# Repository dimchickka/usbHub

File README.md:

# USB PD Charger — 20 портов

Проект KiCad 9.0.6: GD32F470, SDRAM, дисплей 480×272, 20 зарядных USB-C портов.

Открывать **USB_PD_Charger_hw/USB_PD_Charger.kicad_pro**.
Единственная рабочая плата — **USB_PD_Charger_hw/USB_PD_Charger.kicad_pcb**.
Три файла схемы, fp-lib-table, sym-lib-table и каталоги libs входят в проект и нужны для его редактирования. libs/Symbols/ProjectCache содержит рабочие проектные библиотеки, это не временный кеш.

- `USB_PD_Charger_hw/release/FINAL_REVIEW.md` — итоговая проверка и открытые параметры заказа.
- `USB_PD_Charger_hw/release/USB_PD_Charger_fabrication.zip` — Gerber и сверление для изготовления платы.
- `USB_PD_Charger_hw/release/assembly` — справочная BOM и координаты монтажа.
- `USB_PD_Charger_fw` — исходники прошивки.
- `documents` — даташиты.

Финальные DRC, ERC и сверка схемы с платой: 0 ошибок и 0 предупреждений; неподключений 0. Разброс 38 линий SDRAM — 0,727 мм.

Перед заказом выбрать финишное покрытие и согласовать стек 4 слоя / 1,5 мм. F1–F5: выбран Bel 0680H9150-05, 15 А / 125 В DC. Обязательные требования к пяти вводам, БП и испытаниям — в USB_PD_Charger_hw/release/FUSE_SELECTION.md. Нагрузочные испытания устройства на 1 кВт не проводились; геометрическая проверка их не заменяет.

При изменении платы повторить проверки и обновить release. Промежуточные платы, логи трассировки и старые резервные копии вынесены из рабочей директории.

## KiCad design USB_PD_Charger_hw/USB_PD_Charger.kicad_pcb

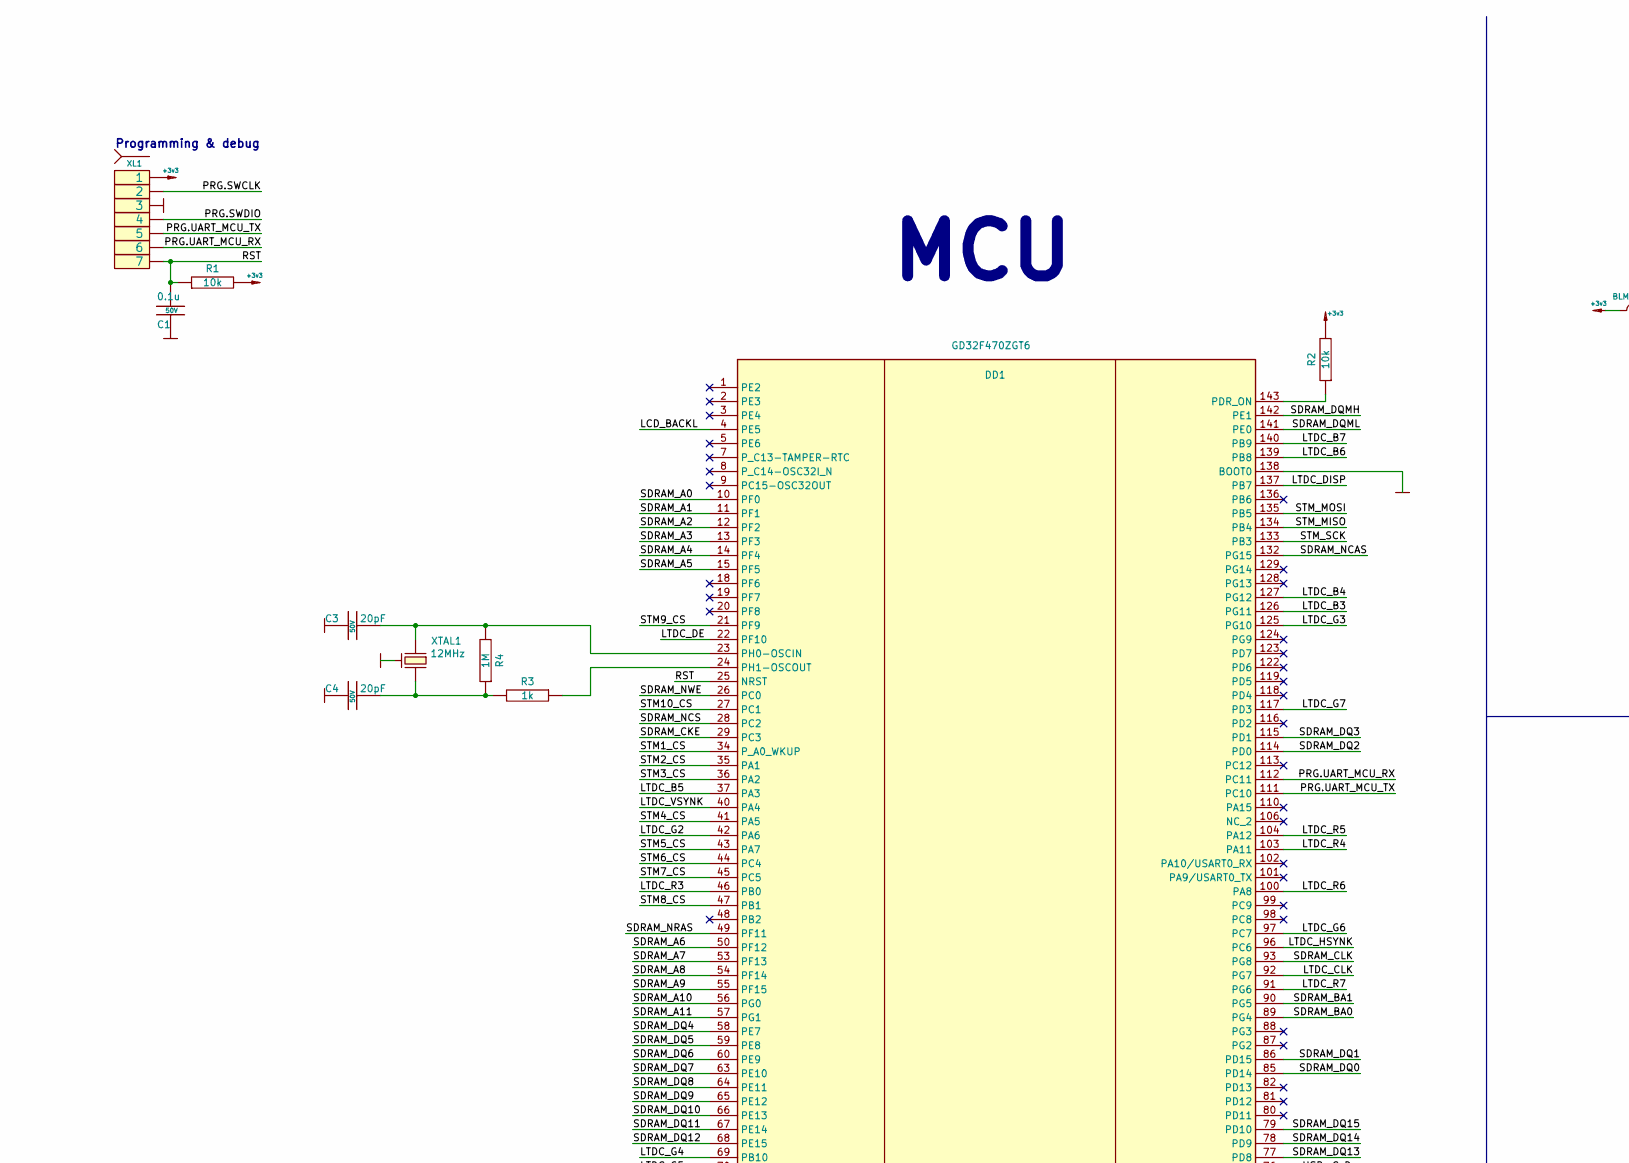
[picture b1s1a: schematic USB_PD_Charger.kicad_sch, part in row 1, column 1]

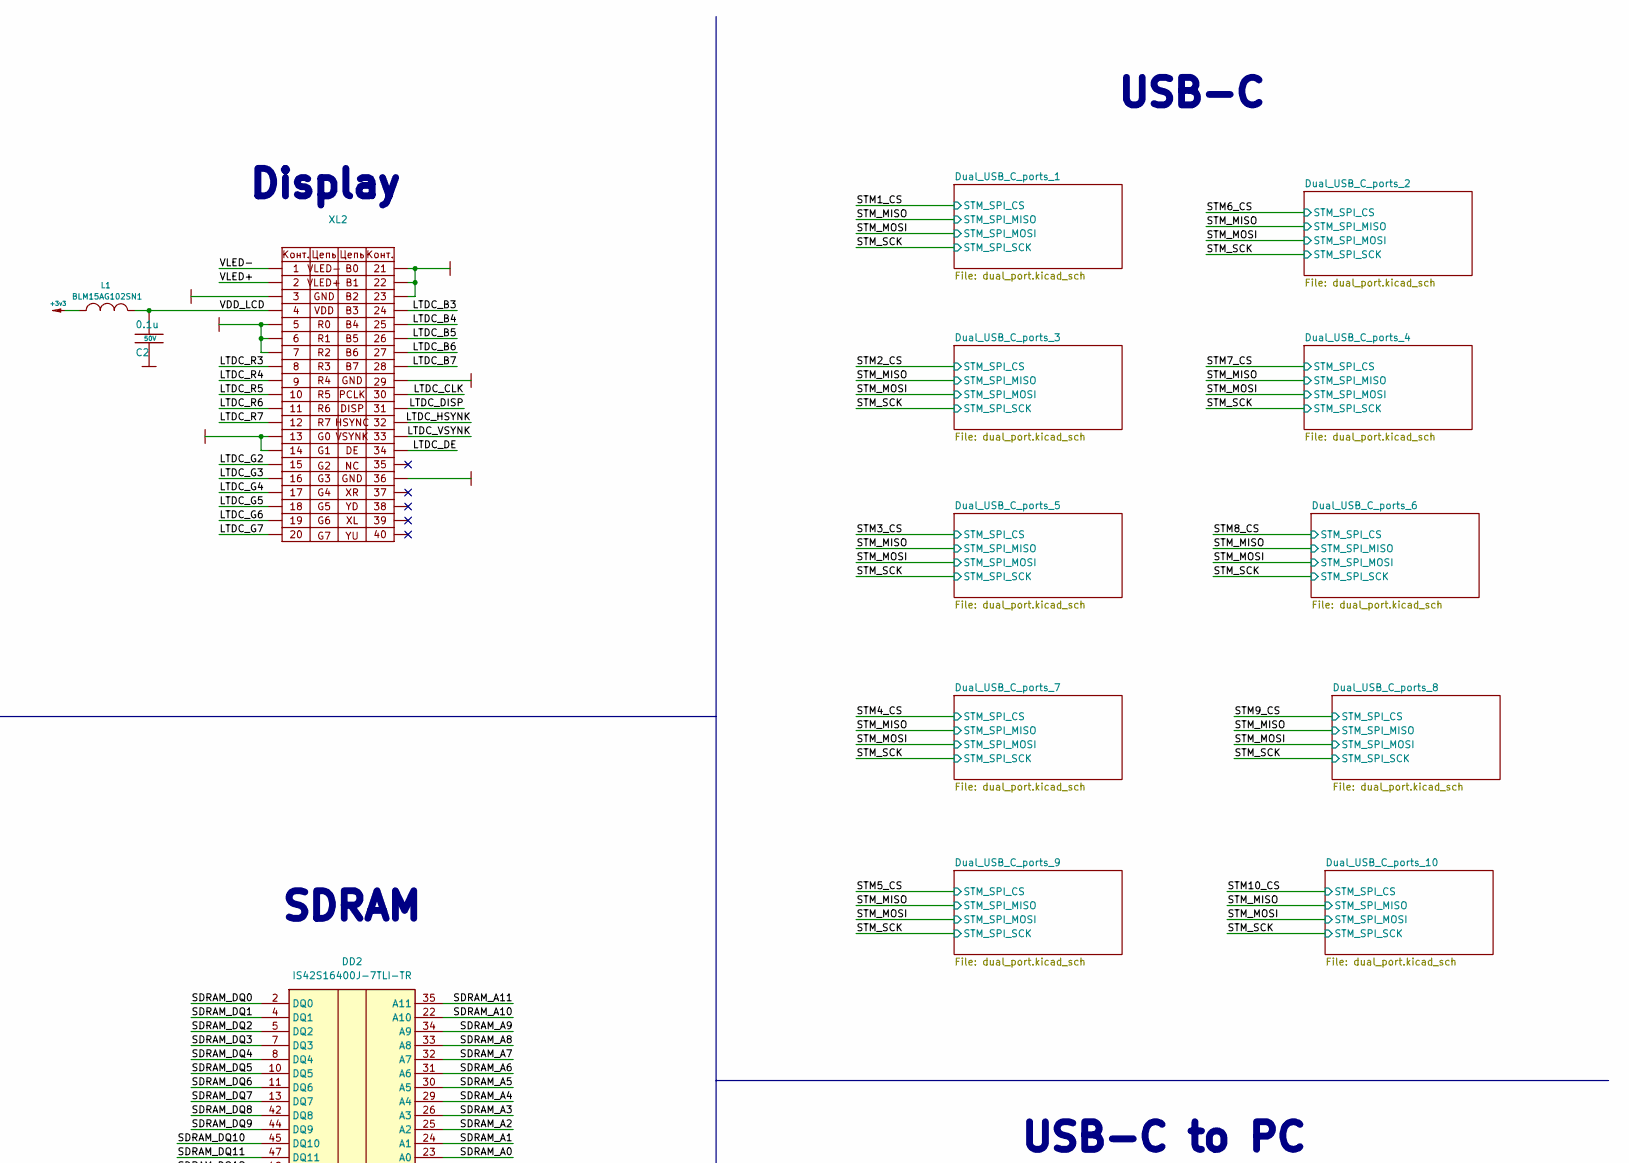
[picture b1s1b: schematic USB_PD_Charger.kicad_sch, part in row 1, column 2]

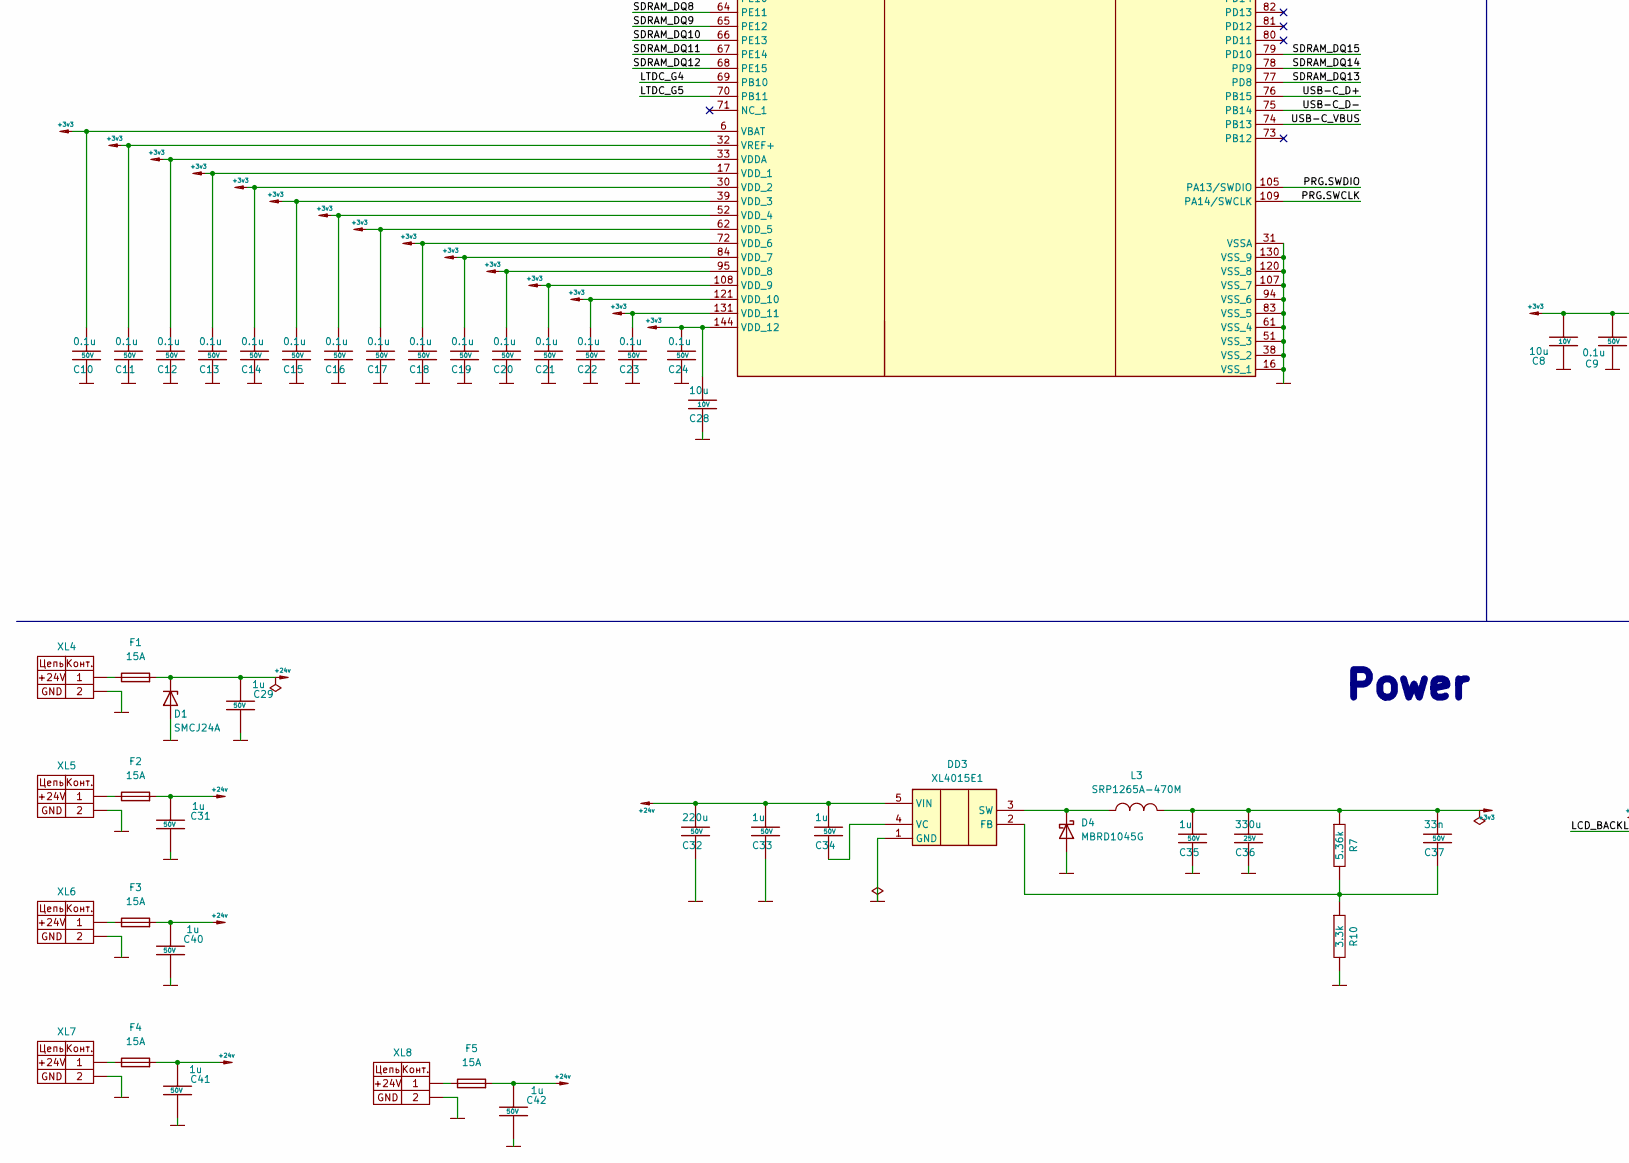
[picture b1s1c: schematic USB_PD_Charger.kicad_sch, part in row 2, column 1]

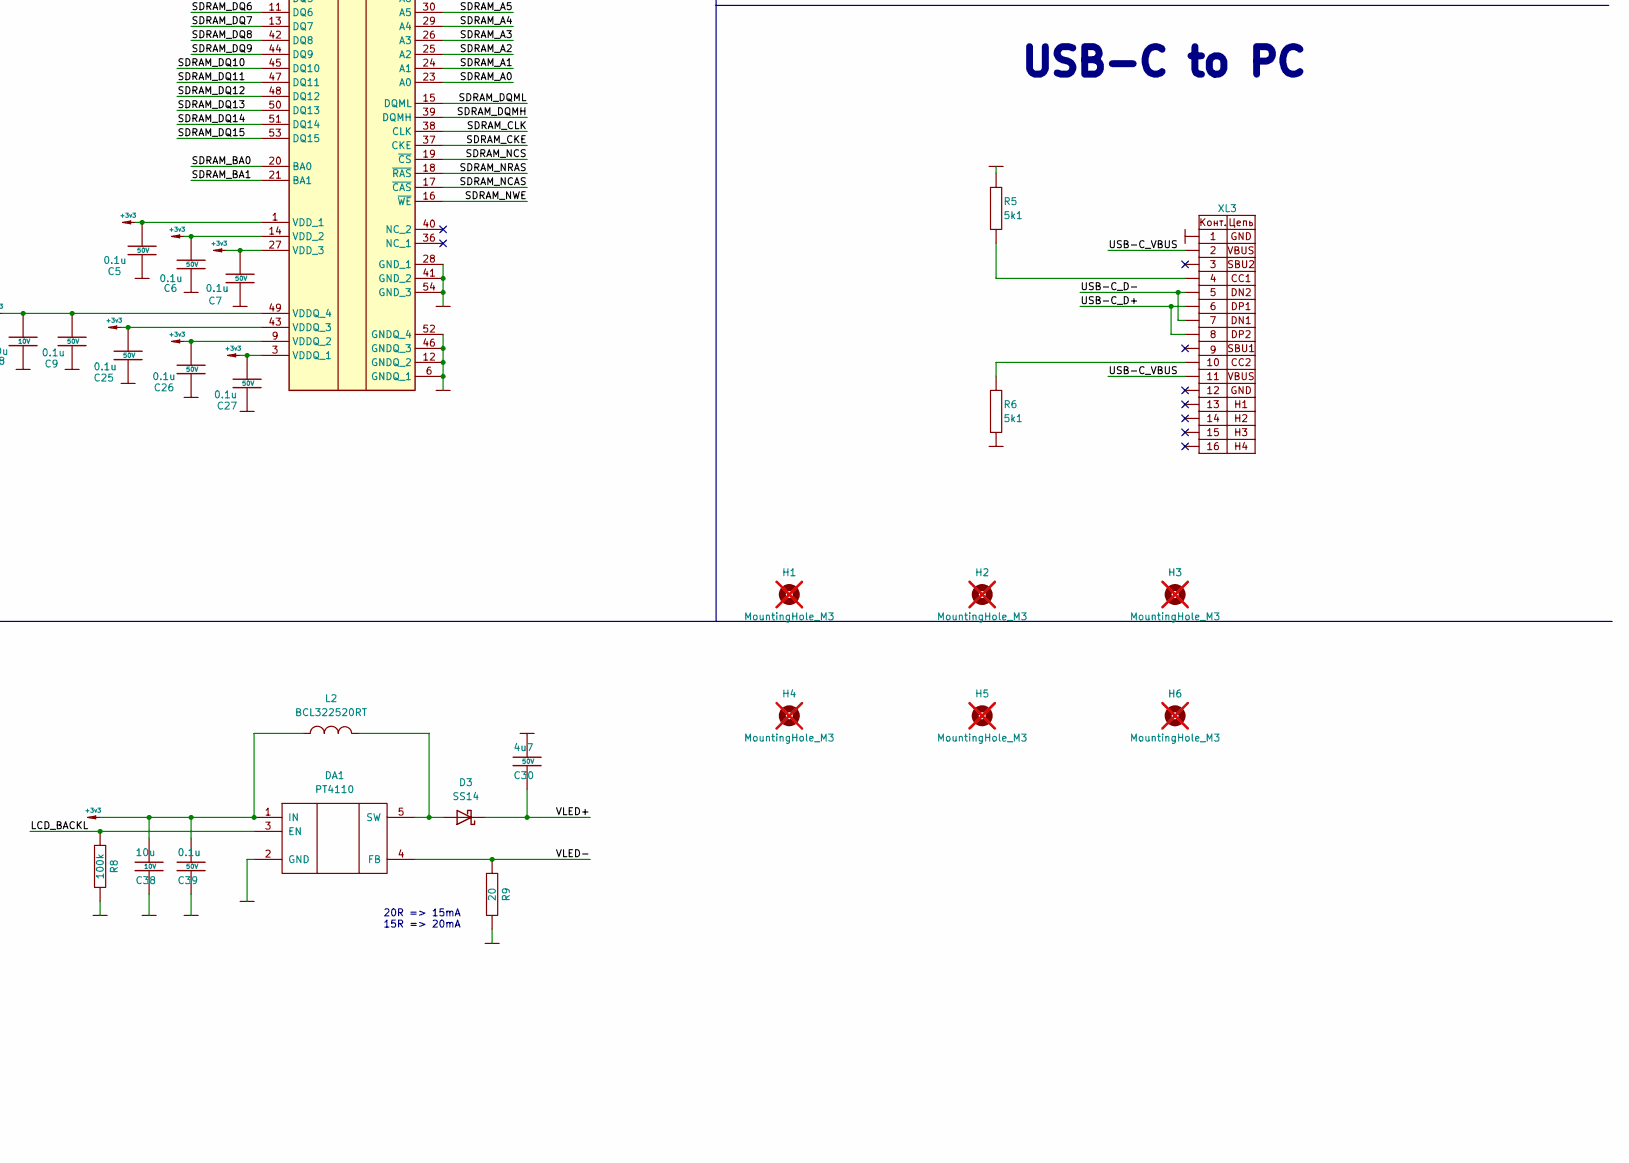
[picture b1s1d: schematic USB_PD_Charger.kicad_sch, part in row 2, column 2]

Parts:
C1: 0.1u; CAP_0603_Silks_Board; Tolerance 10%; Voltage 50V
C2, C5, C6, C7, C9, C10, C11, C12, C13, C14, C15, C16, C17, C18, C19, C20, C21, C22, C23, C24, C25, C26, C27, C39: 0.1u; CAP_0603_Silks; Tolerance 10%; Voltage 50V
C3, C4: 20pF; CAP_0603_Silks; Tolerance 20%; Voltage 50V
C8, C28: 10u; CAP_0603_Silks; Tolerance 20%; Voltage 10V
C29, C31, C33, C34, C35, C40, C41, C42: 1u; CAP_0603_Silks; Tolerance 10%; Voltage 50V
C30: 4u7; C_1206_3216Metric; Tolerance 10%; Voltage 50V
C32: 220u; CP_Elec_10x10.5; Tolerance 10%; Voltage 50V
C36: 330u; CP_Elec_10x10.5; Tolerance 20%; Voltage 25V
C37: 33n; CAP_0603_Silks; Tolerance 10%; Voltage 50V
C38: 10u; CP_EIA-3216-18_Kemet-A; Tolerance 10%; Voltage 10V
D1: SMCJ24A; D_SMB-SMC_Universal_Handsoldering
D3: SS14; D_SMA
D4: MBRD1045G; MBRD1045G_DPAK
DA1: PT4110; SOT89_5_Board
DD1: GD32F470ZGT6; QFP50P2200X2200X160-144N; Manufacturer_Part_Number GD32F470ZGT6
DD2: IS42S16400J-7TLI-TR; SOP80P1176X120-54N; Manufacturer_Part_Number IS42S16400J-7TLI-TR; Mouser Part Number 870-42S16400J7TLITR
DD3: XL4015E1; TO-263-5_TabPin3
F1, F2, F3, F4, F5: 15A; FUSC6125X279N; VoltageRating 125VDC; MPN 0680H9150-05
H1, H2, H3, H4, H5, H6: MountingHole_M3; MountingHole_3.2mm_M3_Clearance7.4; not fitted
L1: BLM15AG102SN1; IND_0402; Tolerance 20%
L2: BCL322520RT; L_1210_3225Metric; Tolerance 20%
L3: SRP1265A-470M; L_TaiTech_TMPC1265_13.5x12.5mm; Tolerance 20%
R1: 10k; RES_0603_Silks_Board; Tolerance 1%
R2: 10k; RES_0603_Silks; Tolerance 1%
R3: 1k; RES_0603_Silks; Tolerance 0.1%
R4: 1M; RES_0603_Silks; Tolerance 1%
R5, R6: 5k1; RES_0603_Silks; Tolerance 1%
R7: 5.36k; RES_0603_Silks; Tolerance 1%
R8: 100k; RES_0603_Silks; Tolerance 1%
R9: 20; RES_0603_Silks; Tolerance 1%
R10: 3.3k; RES_0603_Silks; Tolerance 1%
XL1: SOCKET_7; PLS-7_LOCK
XL2: Omron_XF2M-4015-1A_1x40-1MP_P0.5mm_Horizontal
XL3: USBC_DS1144-18
XL4, XL5, XL6, XL7, XL8: Screw_Terminal; Screw_Terminal_footprint; Manufacturer_Part_Number 1933613; Mouser Part Number 651-1933613
XTAL1: 12MHz; 03225C4

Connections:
+3v3: C5.1, C6.1, C7.1, C8.1, C9.1, C10.1, C11.1, C12.1, C13.1, C14.1, C15.1, C16.1, C17.1, C18.1, C19.1, C20.1, C21.1, C22.1, C23.1, C24.1, C25.1, C26.1, C27.1, C28.1, C35.1, C36.1, C37.1, C38.1, C39.1, DA1.1 (IN), DD1.6 (VBAT), DD1.17 (VDD_1), DD1.30 (VDD_2), DD1.32 (VREF+), DD1.33 (VDDA), DD1.39 (VDD_3), DD1.52 (VDD_4), DD1.62 (VDD_5), DD1.72 (VDD_6), DD1.84 (VDD_7), DD1.95 (VDD_8), DD1.108 (VDD_9), DD1.121 (VDD_10), DD1.131 (VDD_11), DD1.144 (VDD_12), DD2.1 (VDD_1), DD2.3 (VDDQ_1), DD2.9 (VDDQ_2), DD2.14 (VDD_2), DD2.27 (VDD_3), DD2.43 (VDDQ_3), DD2.49 (VDDQ_4), L1.2, L2.2, L3.1, R1.2, R2.2, R7.1, XL1.1; also elsewhere on the board
+24v: C29.2, C31.2, C32.1, C33.1, C34.1, C40.2, C41.2, C42.2, D1.1 (K), DD3.5 (VIN), F1.2, F2.2, F3.2, F4.2, F5.2; also elsewhere on the board
/LCD_BACKL: DA1.3 (EN), DD1.4 (PE5), R8.1
/LTDC_B3: DD1.126 (PG11), XL2.24 (+3.3V)
/LTDC_B4: DD1.127 (PG12), XL2.25 (r8t0)
/LTDC_B5: DD1.37 (PA3), XL2.26 (r8p1)
/LTDC_B6: DD1.139 (PB8), XL2.27 (+3.3V)
/LTDC_B7: DD1.140 (PB9), XL2.28 (r9t0)
/LTDC_CLK: DD1.92 (PG7), XL2.30 (+3.3V)
/LTDC_DE: DD1.22 (PF10), XL2.34 (+3.3V)
/LTDC_DISP: DD1.137 (PB7), XL2.31 (+3.3V)
/LTDC_G2: DD1.42 (PA6), XL2.15 (+3.3V)
/LTDC_G3: DD1.125 (PG10), XL2.20 (r6t1)
/LTDC_G4: DD1.69 (PB10), XL2.19 (r6t0)
/LTDC_G5: DD1.70 (PB11), XL2.18 (+3.3V)
/LTDC_G6: DD1.97 (PC7), XL2.17 (r5t1)
/LTDC_G7: DD1.117 (PD3), XL2.16 (r5t0)
/LTDC_HSYNK: DD1.96 (PC6), XL2.32 (r7t0)
/LTDC_R3: DD1.46 (PB0), XL2.8 (r2t1)
/LTDC_R4: DD1.103 (PA11), XL2.9 (+3.3V)
/LTDC_R5: DD1.104 (PA12), XL2.10 (r3t0)
/LTDC_R6: DD1.100 (PA8), XL2.11 (r3t1)
/LTDC_R7: DD1.91 (PG6), XL2.12 (+3.3V)
/LTDC_VSYNK: DD1.40 (PA4), XL2.33 (r7t1)
/PRG.SWCLK: DD1.109 (PA14/SWCLK), XL1.2
/PRG.SWDIO: DD1.105 (PA13/SWDIO), XL1.4
/PRG.UART_MCU_RX: DD1.112 (PC11), XL1.6
/PRG.UART_MCU_TX: DD1.111 (PC10), XL1.5
/RST: C1.1, DD1.25 (NRST), R1.1, XL1.7
/SDRAM_A0: DD1.10 (PF0), DD2.23 (A0)
/SDRAM_A1: DD1.11 (PF1), DD2.24 (A1)
/SDRAM_A2: DD1.12 (PF2), DD2.25 (A2)
/SDRAM_A3: DD1.13 (PF3), DD2.26 (A3)
/SDRAM_A4: DD1.14 (PF4), DD2.29 (A4)
/SDRAM_A5: DD1.15 (PF5), DD2.30 (A5)
/SDRAM_A6: DD1.50 (PF12), DD2.31 (A6)
/SDRAM_A7: DD1.53 (PF13), DD2.32 (A7)
/SDRAM_A8: DD1.54 (PF14), DD2.33 (A8)
/SDRAM_A9: DD1.55 (PF15), DD2.34 (A9)
/SDRAM_A10: DD1.56 (PG0), DD2.22 (A10)
/SDRAM_A11: DD1.57 (PG1), DD2.35 (A11)
/SDRAM_BA0: DD1.89 (PG4), DD2.20 (BA0)
/SDRAM_BA1: DD1.90 (PG5), DD2.21 (BA1)
/SDRAM_CKE: DD1.29 (PC3), DD2.37 (CKE)
/SDRAM_CLK: DD1.93 (PG8), DD2.38 (CLK)
/SDRAM_DQ0: DD1.85 (PD14), DD2.2 (DQ0)
/SDRAM_DQ1: DD1.86 (PD15), DD2.4 (DQ1)
/SDRAM_DQ2: DD1.114 (PD0), DD2.5 (DQ2)
/SDRAM_DQ3: DD1.115 (PD1), DD2.7 (DQ3)
/SDRAM_DQ4: DD1.58 (PE7), DD2.8 (DQ4)
/SDRAM_DQ5: DD1.59 (PE8), DD2.10 (DQ5)
/SDRAM_DQ6: DD1.60 (PE9), DD2.11 (DQ6)
/SDRAM_DQ7: DD1.63 (PE10), DD2.13 (DQ7)
/SDRAM_DQ8: DD1.64 (PE11), DD2.42 (DQ8)
/SDRAM_DQ9: DD1.65 (PE12), DD2.44 (DQ9)
/SDRAM_DQ10: DD1.66 (PE13), DD2.45 (DQ10)
/SDRAM_DQ11: DD1.67 (PE14), DD2.47 (DQ11)
/SDRAM_DQ12: DD1.68 (PE15), DD2.48 (DQ12)
/SDRAM_DQ13: DD1.77 (PD8), DD2.50 (DQ13)
/SDRAM_DQ14: DD1.78 (PD9), DD2.51 (DQ14)
/SDRAM_DQ15: DD1.79 (PD10), DD2.53 (DQ15)
/SDRAM_DQMH: DD1.142 (PE1), DD2.39 (DQMH)
/SDRAM_DQML: DD1.141 (PE0), DD2.15 (DQML)
/SDRAM_NCAS: DD1.132 (PG15), DD2.17 (~CAS)
/SDRAM_NCS: DD1.28 (PC2), DD2.19 (~CS)
/SDRAM_NRAS: DD1.49 (PF11), DD2.18 (~RAS)
/SDRAM_NWE: DD1.26 (PC0), DD2.16 (~WE)
/STM1_CS: DD1.34 (P_A0_WKUP); also elsewhere on the board
/STM2_CS: DD1.35 (PA1); also elsewhere on the board
/STM3_CS: DD1.36 (PA2); also elsewhere on the board
/STM4_CS: DD1.41 (PA5); also elsewhere on the board
/STM5_CS: DD1.43 (PA7); also elsewhere on the board
/STM6_CS: DD1.44 (PC4); also elsewhere on the board
/STM7_CS: DD1.45 (PC5); also elsewhere on the board
/STM8_CS: DD1.47 (PB1); also elsewhere on the board
/STM9_CS: DD1.21 (PF9); also elsewhere on the board
/STM10_CS: DD1.27 (PC1); also elsewhere on the board
/STM_MISO: DD1.134 (PB4); also elsewhere on the board
/STM_MOSI: DD1.135 (PB5); also elsewhere on the board
/STM_SCK: DD1.133 (PB3); also elsewhere on the board
/USB-C_D+: DD1.76 (PB15), XL3.A6 (+3.3V), XL3.B6 (r2t1)
/USB-C_D-: DD1.75 (PB14), XL3.A7 (r2t0), XL3.B7 (r1t1)
/USB-C_VBUS: DD1.74 (PB13), XL3.A4B9 (rot1), XL3.B4A9 (r3t1)
/VDD_LCD: C2.1, L1.1, XL2.4 (r1t0)
/VLED+: C30.2, D3.1 (K), XL2.2 (rot1)
/VLED-: DA1.4 (FB), R9.1, XL2.1 (rot0)
GND: C1.2, C2.2, C3.2, C4.2, C5.2, C6.2, C7.2, C8.2, C9.2, C10.2, C11.2, C12.2, C13.2, C14.2, C15.2, C16.2, C17.2, C18.2, C19.2, C20.2, C21.2, C22.2, C23.2, C24.2, C25.2, C26.2, C27.2, C28.2, C29.1, C30.1, C31.1, C32.2, C33.2, C35.2, C36.2, C38.2, C39.2, C40.1, C41.1, C42.1, D1.2 (A), D4.2 (A), DA1.2 (GND), DD1.16 (VSS_1), DD1.31 (VSSA), DD1.38 (VSS_2), DD1.51 (VSS_3), DD1.61 (VSS_4), DD1.83 (VSS_5), DD1.94 (VSS_6), DD1.107 (VSS_7), DD1.120 (VSS_8), DD1.130 (VSS_9), DD1.138 (BOOT0), DD2.6 (GNDQ_1), DD2.12 (GNDQ_2), DD2.28 (GND_1), DD2.41 (GND_2), DD2.46 (GNDQ_3), DD2.52 (GNDQ_4), DD2.54 (GND_3), DD3.1 (GND), R5.1, R6.2, R8.2, R9.2, R10.2, XL1.3, XL2.3 (+3.3V), XL2.5 (r1t1), XL2.6 (+3.3V), XL2.7 (r2t0), XL2.13 (r4t0), XL2.14 (r4t1), XL2.21 (+3.3V), XL2.22 (r7t0), XL2.23 (r7t1), XL2.29 (r9t1), XL2.36 (r8p1), XL3.A1B12 (rot0), XL4.2, XL5.2, XL6.2, XL7.2, XL8.2, XTAL1.H; also elsewhere on the board
unnamed: C4.1, R3.2, R4.1, XTAL1.2
unnamed: D3.2 (A), DA1.5 (SW), L2.1
unnamed: D4.1 (K), DD3.3 (SW), L3.2
unnamed: DD1.143 (PDR_ON), R2.1
unnamed: C3.1, DD1.23 (PH0-OSCIN), R4.2, XTAL1.1
unnamed: DD1.24 (PH1-OSCOUT), R3.1
unnamed: C37.2, DD3.2 (FB), R7.2, R10.1
unnamed: C34.2, DD3.4 (VC)
unnamed: F1.1, XL4.1
unnamed: F2.1, XL5.1
unnamed: F3.1, XL6.1
unnamed: F4.1, XL7.1
unnamed: F5.1, XL8.1
unnamed: R6.1, XL3.B5 (r3t0)
unnamed: R5.2, XL3.A5 (r1t0)

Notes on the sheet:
SDRAM
USB-C to PC
20R => 15mA 15R => 20mA
Power
Programming & debug
MCU
USB-C
Display
